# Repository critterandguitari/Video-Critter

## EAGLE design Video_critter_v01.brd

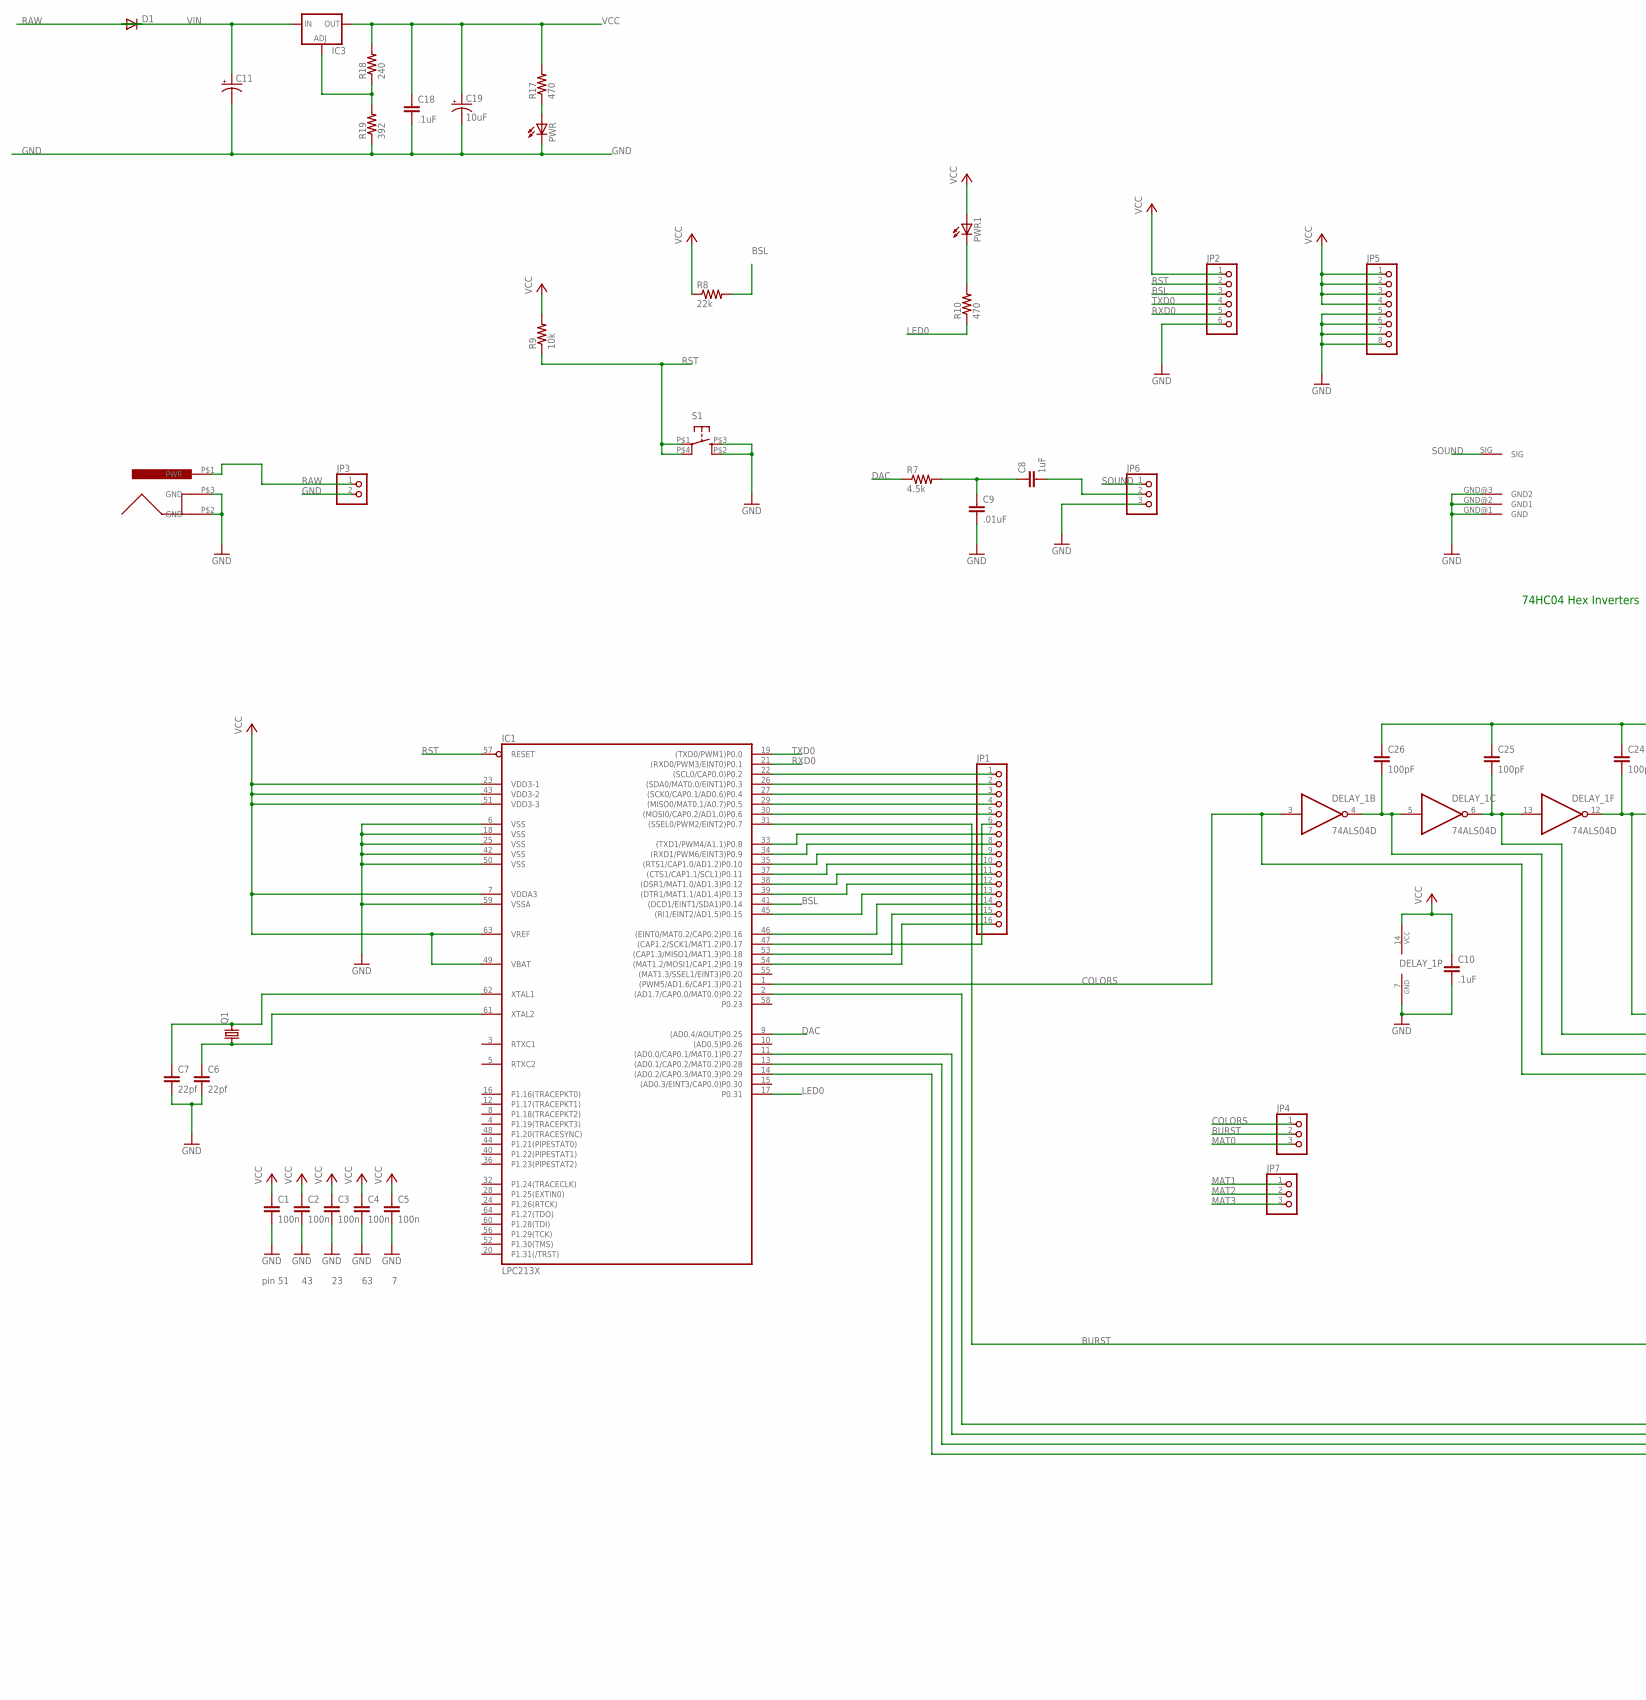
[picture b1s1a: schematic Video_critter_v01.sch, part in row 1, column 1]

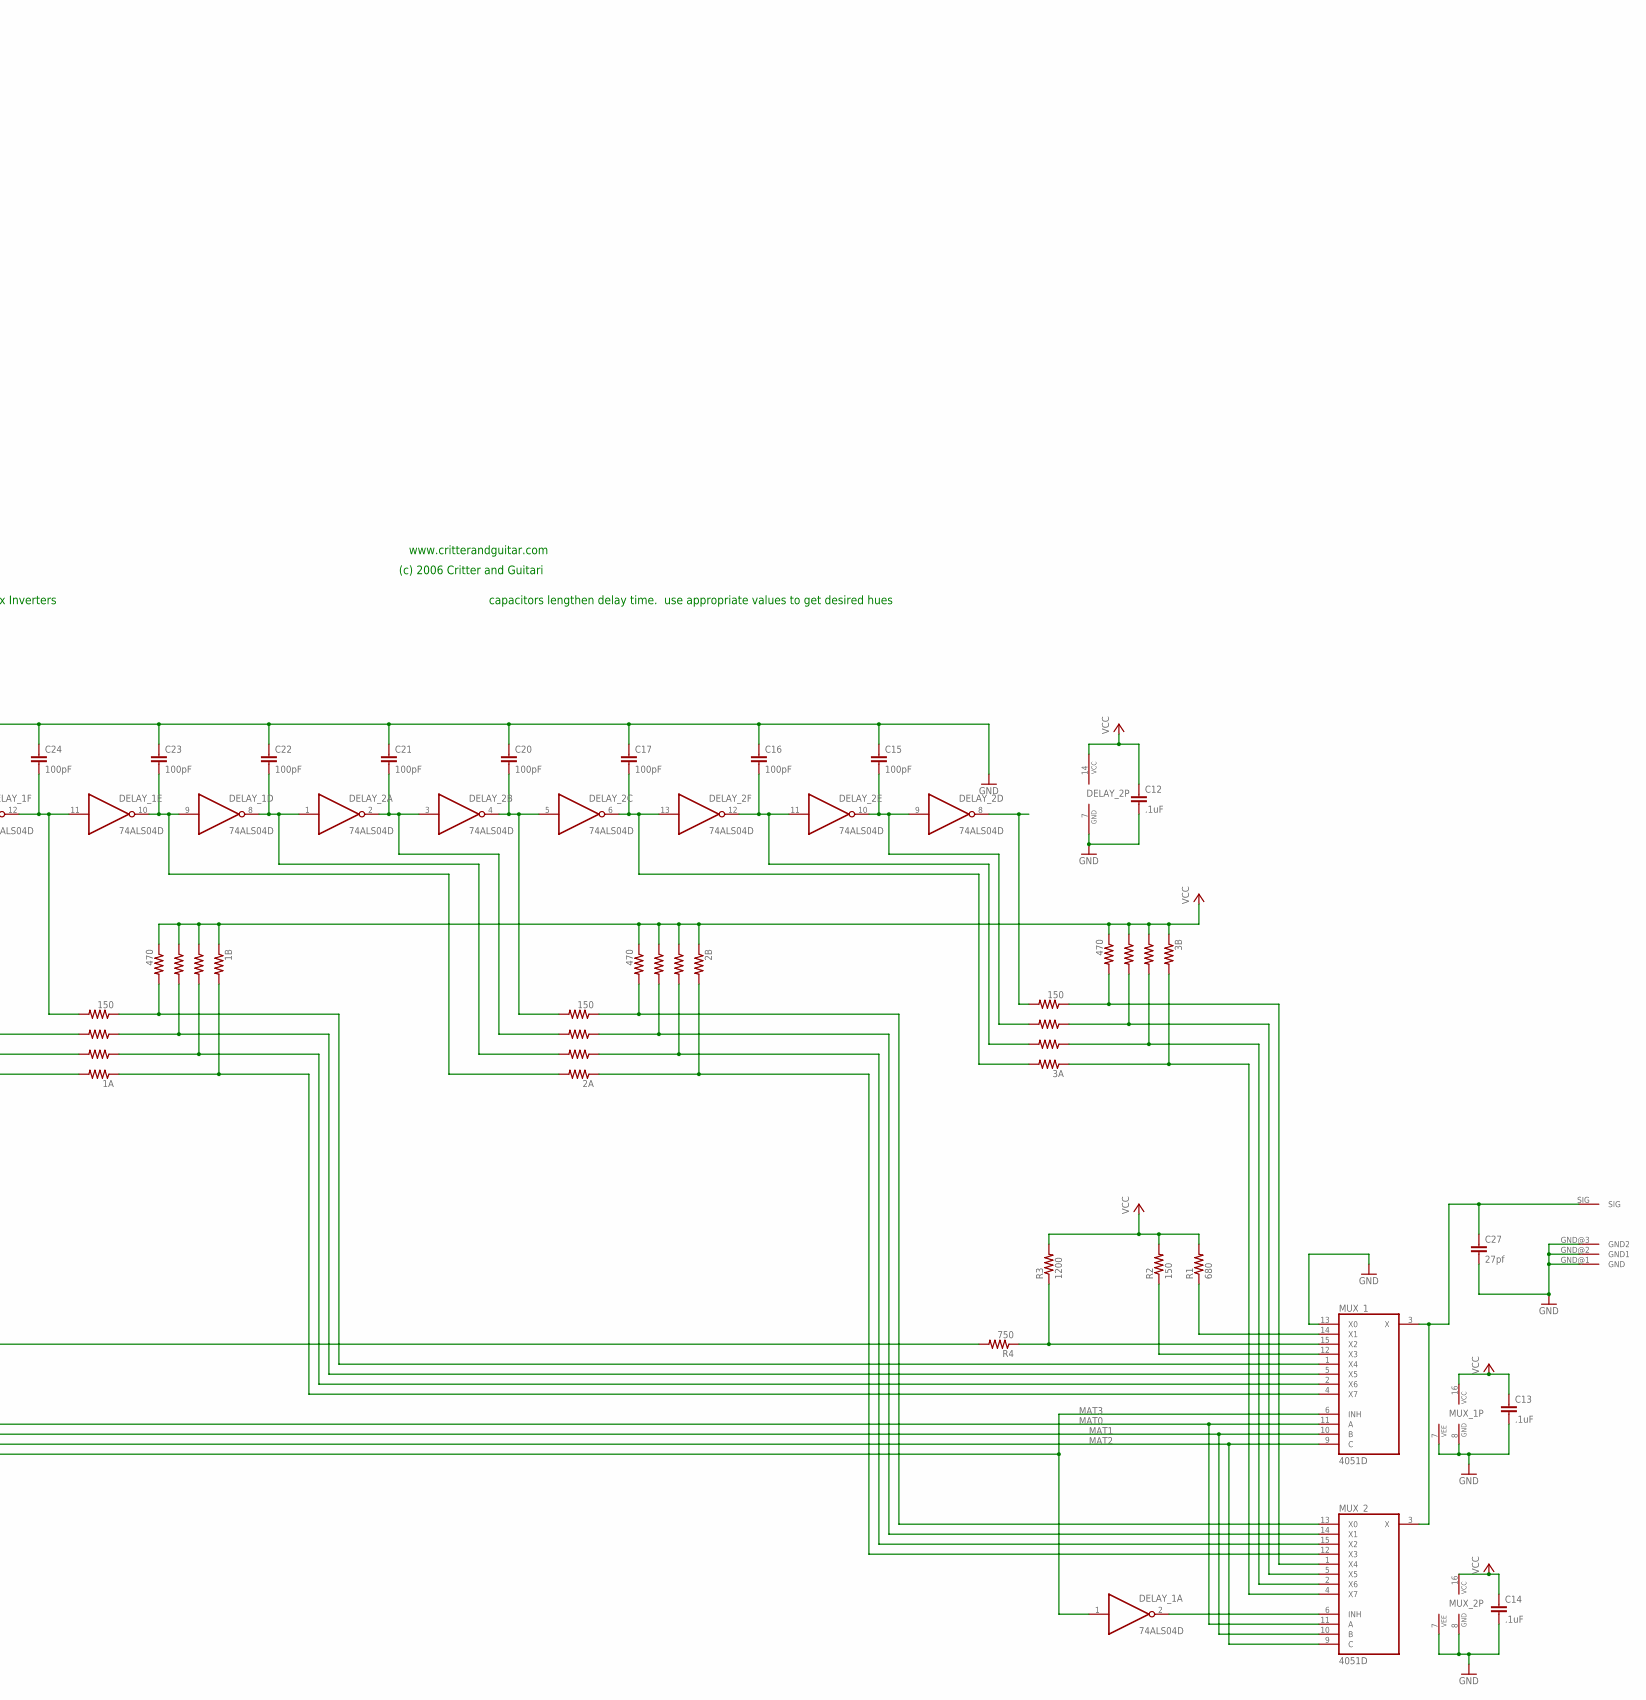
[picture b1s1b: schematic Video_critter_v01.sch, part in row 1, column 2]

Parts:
1A, 2A, 3A: 150; 1206X4RESISTOR
1B, 2B, 3B: 470; 1206X4RESISTOR
C1, C2, C3, C4, C5: 100n; C0603
C6, C7: 22pf; C0603
C8: 1uF; C0603
C9: .01uF; C0603
C10, C12, C13, C14, C18: .1uF; C0603
C11: CPOL-USE3.5-8; E3,5-8
C15, C16, C17, C20, C21, C22, C23, C24, C25, C26: 100pF; C0603
C19: 10uF; CPOL_1206
C27: 27pf; C0603
D1: DIODESMB; SMB
DELAY_1, DELAY_2: 74ALS04D; SO14
IC1: LPC213X; SQFP-S-10X10-64
IC3: V_REG_FAN1117SOT223; SOT223
JP1: PINHD-1X16; 1X16
JP2: PINHD-1X6; 1X06
JP3: PINHD-1X2; 1X02
JP4, JP6, JP7: PINHD-1X3; 1X03
JP5: PINHD-1X8; 1X08
MUX_1, MUX_2: 4051D; SO16
PWR, PWR1: LED1206; CHIPLED_1206
Q1: CRYSTALSOCKETED; HC49U-SOCKETED
R1: 680; R0603
R2: 150; R0603
R3: 1200; R0603
R4: 750; R0603
R7: 4.5k; R0603
R8: 22k; R0603
R9: 10k; R0603
R10, R17: 470; R0603
R18: 240; R0603
R19: 392; R0603
S1: TAC_SWITCH; TACTILE_SWITCH_SMD
U$1: POWER_JACK
U$5, U$6: PHONO_PLUG; PHONO_PCB

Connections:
3B: 3A.P$5 (4), 3B.P$6 (3), MUX_2.2 (X6)
BSL: IC1.41 ((DCD1/EINT1/SDA1)P0.14), JP2.3, R8.2
BURST: IC1.31 ((SSEL0/PWM2/EINT2)P0.7), JP4.2, R4.2
COLORS: 1A.P$8 (7), DELAY_1.3 (I), IC1.1 ((PWM5/AD1.6/CAP1.3)P0.21), JP4.1
DAC: IC1.9 ((AD0.4/AOUT)P0.25), R7.1
GND: C1.2, C2.2, C3.2, C4.2, C5.2, C6.2, C7.2, C9.2, C10.2, C11.-, C12.2, C13.2, C14.2, C15.1, C16.1, C17.1, C18.2, C19.C (-), C20.1, C21.1, C22.1, C23.1, C24.1, C25.1, C26.1, C27.2, DELAY_1.7 (GND), DELAY_2.7 (GND), IC1.6 (VSS), IC1.18 (VSS), IC1.25 (VSS), IC1.42 (VSS), IC1.50 (VSS), IC1.59 (VSSA), JP2.6, JP3.2, JP5.5, JP5.6, JP5.7, JP5.8, JP6.3, MUX_1.7 (VEE), MUX_1.8 (GND), MUX_1.13 (X0), MUX_2.7 (VEE), MUX_2.8 (GND), PWR.C, R19.1, S1.P$2 (S1), S1.P$3 (S), U$1.P$2 (GND), U$1.P$3 (GND), U$5.GND@1 (GND), U$5.GND@2 (GND1), U$5.GND@3 (GND2), U$6.GND@1 (GND), U$6.GND@2 (GND1), U$6.GND@3 (GND2)
LED0: IC1.17 (P0.31), R10.1
MAT0: IC1.2 ((AD1.7/CAP0.0/MAT0.0)P0.22), JP4.3, MUX_1.11 (A), MUX_2.11 (A)
MAT1: IC1.11 ((AD0.0/CAP0.1/MAT0.1)P0.27), JP7.1, MUX_1.10 (B), MUX_2.10 (B)
MAT2: IC1.13 ((AD0.1/CAP0.2/MAT0.2)P0.28), JP7.2, MUX_1.9 (C), MUX_2.9 (C)
MAT3: DELAY_1.1 (I), IC1.14 ((AD0.2/CAP0.3/MAT0.3)P0.29), JP7.3, MUX_1.6 (INH)
unnamed: C8.1, C9.1, R7.2
unnamed: C7.1, IC1.62 (XTAL1), Q1.2
unnamed: C6.1, IC1.61 (XTAL2), Q1.1
unnamed: PWR1.C, R10.2
unnamed: IC1.47 ((CAP1.2/SCK1/MAT1.2)P0.17), JP1.6
unnamed: IC1.22 ((SCL0/CAP0.0)P0.2), JP1.1
unnamed: C8.2, JP6.2
unnamed: 1A.P$6 (3), C26.2, DELAY_1.4 (O), DELAY_1.5 (I)
unnamed: IC1.26 ((SDA0/MAT0.0/EINT1)P0.3), JP1.2
unnamed: IC1.27 ((SCK0/CAP0.1/AD0.6)P0.4), JP1.3
unnamed: IC3.1 (ADJ), R18.1, R19.2
unnamed: IC1.29 ((MISO0/MAT0.1/A0.7)P0.5), JP1.4
unnamed: IC1.30 ((MOSI0/CAP0.2/AD1.0)P0.6), JP1.5
unnamed: IC1.33 ((TXD1/PWM4/A1.1)P0.8), JP1.7
unnamed: IC1.34 ((RXD1/PWM6/EINT3)P0.9), JP1.8
unnamed: IC1.35 ((RTS1/CAP1.0/AD1.2)P0.10), JP1.9
unnamed: IC1.37 ((CTS1/CAP1.1/SCL1)P0.11), JP1.10
unnamed: IC1.38 ((DSR1/MAT1.0/AD1.3)P0.12), JP1.11
unnamed: IC1.39 ((DTR1/MAT1.1/AD1.4)P0.13), JP1.12
unnamed: IC1.45 ((RI1/EINT2/AD1.5)P0.15), JP1.13
unnamed: IC1.46 ((EINT0/MAT0.2/CAP0.2)P0.16), JP1.14
unnamed: IC1.53 ((CAP1.3/MISO1/MAT1.3)P0.18), JP1.15
unnamed: PWR.A, R17.1
unnamed: IC1.54 ((MAT1.2/MOSI1/CAP1.2)P0.19), JP1.16
unnamed: 1A.P$4 (2), C25.2, DELAY_1.6 (O), DELAY_1.13 (I)
unnamed: 1A.P$2 (5), C24.2, DELAY_1.11 (I), DELAY_1.12 (O)
unnamed: 2A.P$8 (7), C23.2, DELAY_1.9 (I), DELAY_1.10 (O)
unnamed: 2A.P$6 (3), C22.2, DELAY_1.8 (O), DELAY_2.1 (I)
unnamed: 2A.P$4 (2), C21.2, DELAY_2.2 (O), DELAY_2.3 (I)
unnamed: 2A.P$2 (5), C20.2, DELAY_2.4 (O), DELAY_2.5 (I)
unnamed: 3A.P$8 (7), C17.2, DELAY_2.6 (O), DELAY_2.13 (I)
unnamed: 3A.P$6 (3), C16.2, DELAY_2.11 (I), DELAY_2.12 (O)
unnamed: 3A.P$4 (2), C15.2, DELAY_2.9 (I), DELAY_2.10 (O)
unnamed: 3A.P$2 (5), DELAY_2.8 (O)
unnamed: 1A.P$1 (6), 1B.P$2 (5), MUX_1.1 (X4)
unnamed: 1A.P$3 (1), 1B.P$4 (2), MUX_1.5 (X5)
unnamed: 1A.P$5 (4), 1B.P$6 (3), MUX_1.2 (X6)
unnamed: 1A.P$7 (8), 1B.P$8 (7), MUX_1.4 (X7)
unnamed: 2A.P$1 (6), 2B.P$2 (5), MUX_2.13 (X0)
unnamed: 2A.P$3 (1), 2B.P$4 (2), MUX_2.14 (X1)
unnamed: 2A.P$5 (4), 2B.P$6 (3), MUX_2.15 (X2)
unnamed: 2A.P$7 (8), 2B.P$8 (7), MUX_2.12 (X3)
unnamed: 3A.P$1 (6), 3B.P$2 (5), MUX_2.1 (X4)
unnamed: 3A.P$3 (1), 3B.P$4 (2), MUX_2.5 (X5)
unnamed: C27.1, MUX_1.3 (X), MUX_2.3 (X), U$6.SIG
unnamed: 3A.P$7 (8), 3B.P$8 (7), MUX_2.4 (X7)
unnamed: DELAY_1.2 (O), MUX_2.6 (INH)
unnamed: MUX_1.15 (X2), R3.1, R4.1
unnamed: MUX_1.12 (X3), R2.1
unnamed: MUX_1.14 (X1), R1.1
RAW: D1.1 (C), JP3.1, U$1.P$1 (PWR)
RST: IC1.57 (RESET), JP2.2, R9.1, S1.P$1, S1.P$4 (P1)
RXD0: IC1.21 ((RXD0/PWM3/EINT0)P0.1), JP2.5
SOUND: JP6.1, U$5.SIG
TXD0: IC1.19 ((TXD0/PWM1)P0.0), JP2.4
VCC: 1B.P$1 (6), 1B.P$3 (1), 1B.P$5 (4), 1B.P$7 (8), 2B.P$1 (6), 2B.P$3 (1), 2B.P$5 (4), 2B.P$7 (8), 3B.P$1 (6), 3B.P$3 (1), 3B.P$5 (4), 3B.P$7 (8), C1.1, C2.1, C3.1, C4.1, C5.1, C10.1, C12.1, C13.1, C14.1, C18.1, C19.A (+), DELAY_1.14 (VCC), DELAY_2.14 (VCC), IC1.7 (VDDA3), IC1.23 (VDD3-1), IC1.43 (VDD3-2), IC1.49 (VBAT), IC1.51 (VDD3-3), IC1.63 (VREF), IC3.2 (OUT), JP2.1, JP5.1, JP5.2, JP5.3, JP5.4, MUX_1.16 (VCC), MUX_2.16 (VCC), PWR1.A, R1.2, R2.2, R3.2, R8.1, R9.2, R17.2, R18.2
VIN: C11.+, D1.2 (A), IC3.3 (IN)

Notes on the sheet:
pin 51
74HC04 Hex Inverters
capacitors lengthen delay time. use appropriate values to get desired hues
www.critterandguitar.com
(c) 2006 Critter and Guitari

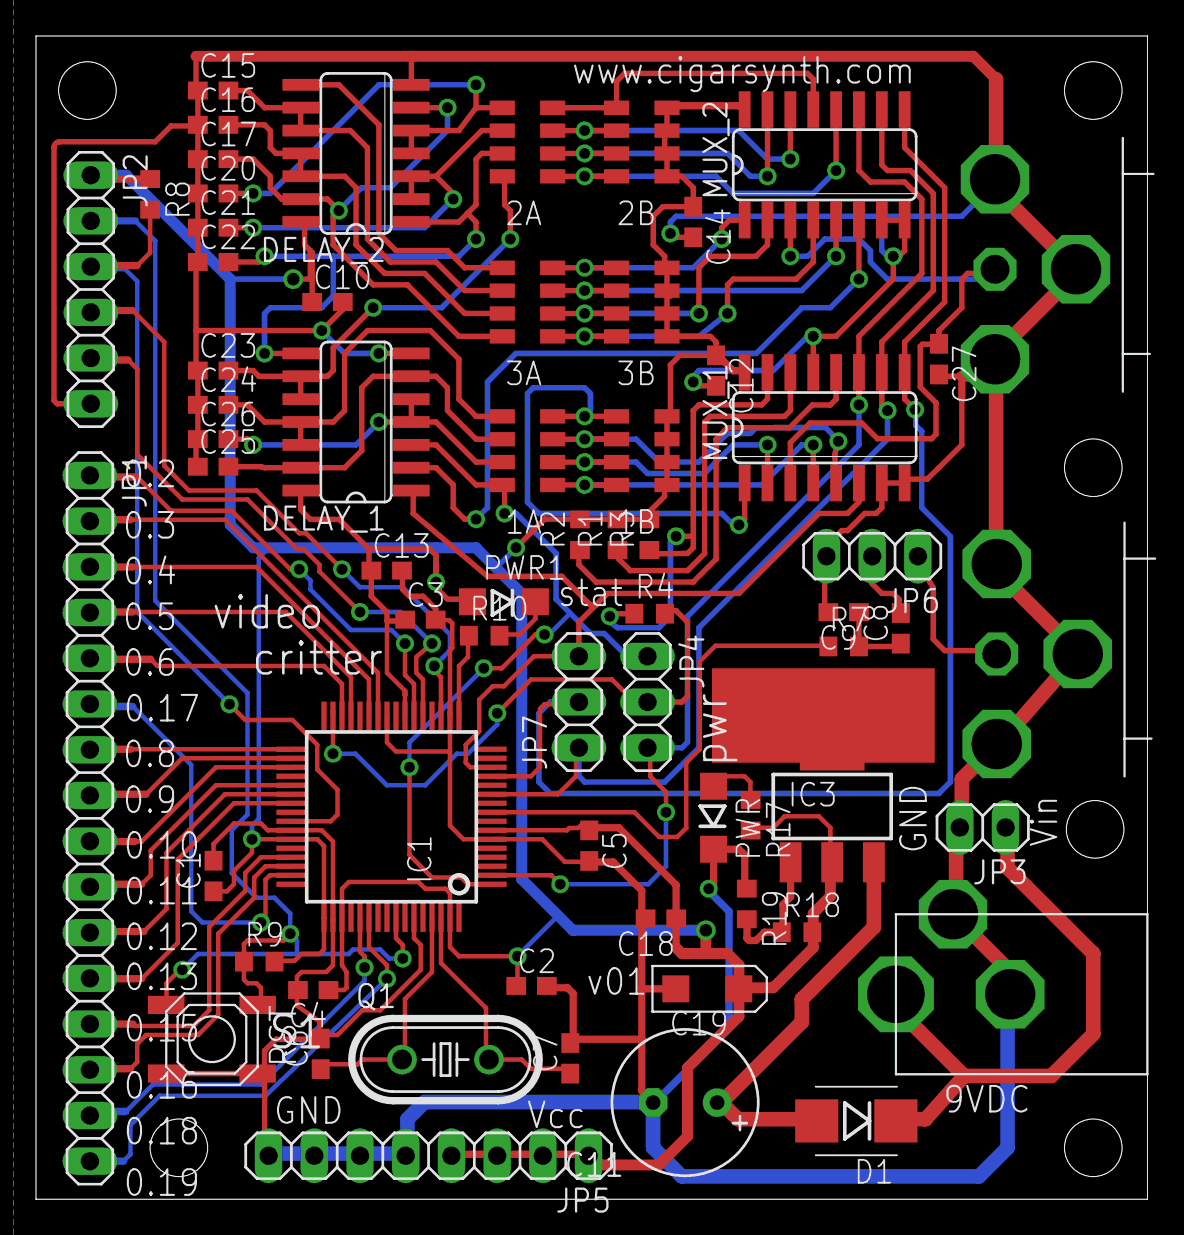
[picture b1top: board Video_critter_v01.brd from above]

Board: 2 copper layers, 61.8 x 64.6 mm, 65 parts (0 on the bottom side), 68 nets.

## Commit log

2013-04-22 adding eagle files
